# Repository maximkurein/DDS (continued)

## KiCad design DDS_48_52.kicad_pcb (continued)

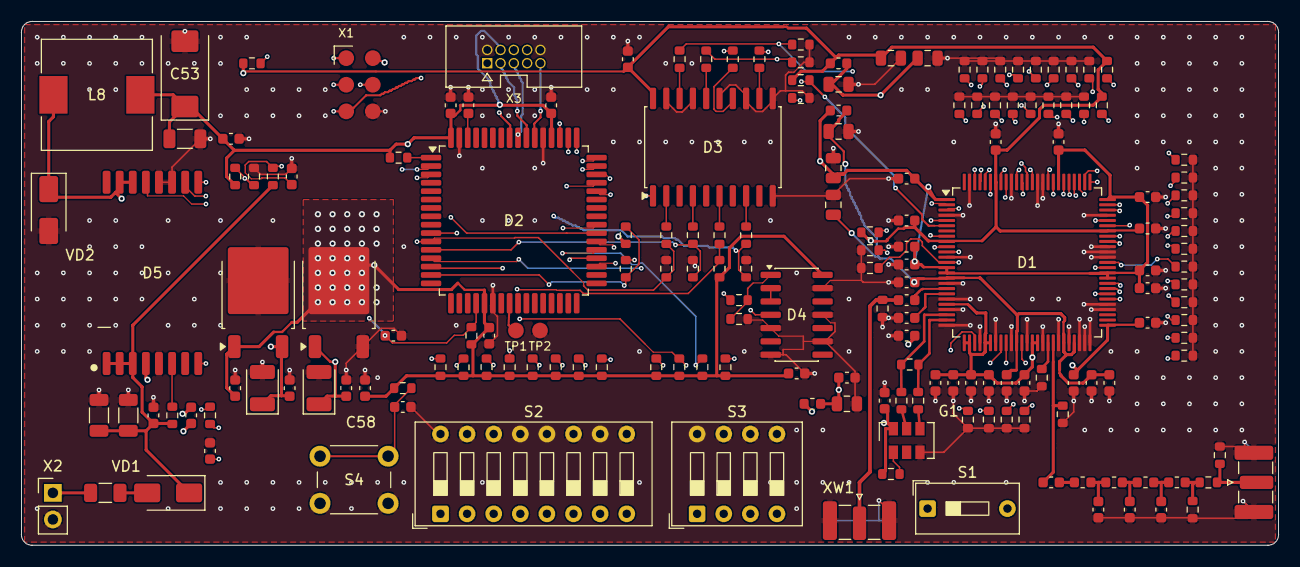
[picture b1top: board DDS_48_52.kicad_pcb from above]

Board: 4 copper layers, 120.0 x 50.0 mm, 178 parts (0 on the bottom side), 116 nets.

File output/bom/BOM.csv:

"Reference","Value","Footprint","Допуск","Мощность","Напряжение","ТКЕ","Примечание","QUANTITY","DNP"
"C1,C55,C56","1u","Capacitor_SMD:C_0603_1608Metric","","","16V","X7R","","3",""
"C2,C12-C18,C20-C23,C25-C27,C29-C36,C38-C45,C48,C50,C51,C54,C59,C60","100n","Capacitor_SMD:C_0603_1608Metric","","","50V","X7R","","37",""
"C3-C5","10n","Capacitor_SMD:C_0603_1608Metric","","","50V","C0G","","3",""
"C6,C11","56p","Capacitor_SMD:C_0603_1608Metric","2%","","50V","C0G","","2",""
"C7","91p","Capacitor_SMD:C_0603_1608Metric","2%","","50V","C0G","","1",""
"C8-C10,C19,C24,C28,C37","10u","Capacitor_SMD:C_0805_2012Metric","","","10V","X7R","","7",""
"C46,C47","10u","Capacitor_SMD:C_1206_3216Metric","","","25V","X7R","","2",""
"C49","220n","Capacitor_SMD:C_0603_1608Metric","","","50V","X7R","","1",""
"C52","22u","Capacitor_SMD:C_1206_3216Metric","","","10V","X7R","","1",""
"C53","100u","Capacitor_Tantalum_SMD:CP_EIA-7343-31_Kemet-D","","","10V","","танталовый (К53-65 — уточнить типоразмер); ESR задаёт ноль коррекции","1",""
"C57,C58","10u","Capacitor_Tantalum_SMD:CP_EIA-3528-21_Kemet-B","","","10V","","танталовый (К53-65 — уточнить типоразмер)","2",""
"D1","1508ПЛ8Т","DDS:LQFP-100_14x14mm_P0.5mm_1508PL8T","","","","","","1",""
"D2","1887ВЕ7Т","DDS:CQFP-64_4203.64-2_14x14mm_P0.8mm_1887VE7T","","","","","","1",""
"D3","1564АП3У2","DDS:SOIC-20W_1564AP3U2_PLACEHOLDER","","","","","буфер 5 -> 3,3 В, питание +3,3 В","1",""
"D4","1594ТЛ2Т","DDS:SOIC-14_1594TL2T_PLACEHOLDER","","","","","SDO 3,3 -> 5 В, питание +5 В","1",""
"D5","1393ЕУ014","DDS:4112.16-15.01_1393EU014_PLACEHOLDER","","","","","DC/DC +15 -> +5 В; корпус 4112.16-15.01 — посадочное место уточнить по чертежу","1",""
"D6","1158ЕН3.3ВХ","DDS:KT-93-1_PLACEHOLDER","","","","","LDO +3,3 В","1",""
"D7","1325ЕН1.8У","DDS:KT-93-1_PLACEHOLDER","","","","","LDO +1,8 В","1",""
"F1","0.5A","Fuse:Fuse_1206_3216Metric","","","","","","1",""
"G1","ГК361-ТК-02","DDS:OSC_6pad_5.0x3.2mm_P1.27mm_GK361_UNVERIFIED","","","","","480 МГц LVDS; распиновка и корпус НЕ ПОДТВЕРЖДЕНЫ паспортом","1","DNP"
"L1,L7","51n","Inductor_SMD:L_0603_1608Metric","2%","","","","ВЧ, Q >= 30 на 50 МГц","2",""
"L2-L4","600R@100MHz","Inductor_SMD:L_0603_1608Metric","","","","","ферритовый фильтр, Rdc <= 0,1 Ом, 1 А","3",""
"L5,L6","200n","Inductor_SMD:L_0603_1608Metric","2%","","","","ВЧ, Q >= 30 на 50 МГц","2",""
"L8","56u","DDS:L_10.4x10.4_L8_UNSELECTED_PLACEHOLDER","","","","","Силовой 56 мкГн; тип по перечню Минпромторга НЕ ВЫБРАН; ТУ и корпус уточнить","1",""
"R1","10k","Resistor_SMD:R_0603_1608Metric","5%","0,063 Вт","","","","1","DNP"
"R2","49.9R","Resistor_SMD:R_0603_1608Metric","1%","0,063 Вт","","","","1",""
"R3,R4","0R","Resistor_SMD:R_0603_1608Metric","","0,063 Вт","","","","2","DNP"
"R5,R7-R9,R48-R64,R67,R69,R72,R77-R80,R85","10k","Resistor_SMD:R_0603_1608Metric","5%","0,063 Вт","","","","29",""
"R6","100R","Resistor_SMD:R_0603_1608Metric","1%","0,063 Вт","","","","1",""
"R10,R13-R24,R28-R43,R82,R84","100k","Resistor_SMD:R_0603_1608Metric","5%","0,063 Вт","","","","31",""
"R11,R12","7.15k","Resistor_SMD:R_0603_1608Metric","0,1%","0,063 Вт","","","задаёт IFS = 72 В / R = 10,07 мА","2",""
"R25-R27,R44","49.9R","Resistor_SMD:R_0603_1608Metric","0,1%","0,063 Вт","","","","4",""
"R45","5.76R","Resistor_SMD:R_0603_1608Metric","1%","0,063 Вт","","","","1",""
"R46,R47","866R","Resistor_SMD:R_0603_1608Metric","1%","0,063 Вт","","","","2",""
"R65,R66,R68,R70,R71","1k","Resistor_SMD:R_0603_1608Metric","5%","0,063 Вт","","","ограничение тока защитных диодов 1564АП3","5",""
"R73-R76","33R","Resistor_SMD:R_0603_1608Metric","5%","0,063 Вт","","","","4",""
"R81","1k","Resistor_SMD:R_0603_1608Metric","5%","0,063 Вт","","","","1",""
"R83","909R","Resistor_SMD:R_0603_1608Metric","1%","0,063 Вт","","","порог тока ключа ≈ 1,6 А","1",""
"R86","40.2k","Resistor_SMD:R_0603_1608Metric","1%","0,063 Вт","","","","1",""
"R87","10k","Resistor_SMD:R_0603_1608Metric","1%","0,063 Вт","","","","1",""
"R88","47k","Resistor_SMD:R_0603_1608Metric","5%","0,063 Вт","","","признак +3,3 В для МК","1",""
"S1","DIP-1","Button_Switch_THT:SW_DIP_SPSTx01_Slide_9.78x4.72mm_W7.62mm_P2.54mm","","","","","CSEL: замкнут = внешний такт (XW1)","1",""
"S2","DIP-8","Button_Switch_THT:SW_DIP_SPSTx08_Slide_9.78x22.5mm_W7.62mm_P2.54mm","","","","","биты 0–7 кода частоты","1",""
"S3","DIP-4","Button_Switch_THT:SW_DIP_SPSTx04_Slide_9.78x12.34mm_W7.62mm_P2.54mm","","","","","биты 8–11 кода частоты","1",""
"S4","6x6","Button_Switch_THT:SW_PUSH_6mm","","","","","«Применить»","1",""
"VD1","SS34","Diode_SMD:D_SMA","","","","","","1",""
"VD2","2Д2990А","DDS:D_SMA_2D2990A_PLACEHOLDER","","","","","диод DC/DC: >= 2 А, >= 40 В (параметры и корпус — уточнить по ТУ)","1",""
"X2","PLS-2","Connector_PinHeader_2.54mm:PinHeader_1x02_P2.54mm_Vertical","","","","","вход +15 В","1",""
"X3","SHF-105-01-L-D-TH","DDS:Samtec_SHF-105-01-L-D-TH","","","","","AVR JTAG Atmel-ICE, 2x5, шаг 1,27 мм; VTG только контроль +5 В","1",""
"XW1","SMA","Connector_Coaxial:SMA_Samtec_SMA-J-P-H-ST-EM1_EdgeMount","","","","","вход 480 МГц, 0 дБм, 50 Ом","1",""
"XW2","SMA","Connector_Coaxial:SMA_Samtec_SMA-J-P-H-ST-EM1_EdgeMount","","","","","выход 48–52 МГц, −10 дБм, 50 Ом","1",""

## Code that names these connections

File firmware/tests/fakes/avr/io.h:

/* Host-only register stand-ins; selected by the regression test include path. */
#ifndef TEST_AVR_IO_H
#define TEST_AVR_IO_H
#include <stdint.h>
#define _BV(bit) (1u << (bit))
enum { PB0, PB1, PB2, PB3, PB4, PB5, PB6, PB7 };
enum { PC0, PC1, PC2, PC3, PC4, PC5, PC6, PC7 };
extern uint8_t PORTA, DDRA, PINA, PORTB, DDRB, PINB, PORTC, DDRC, PINC;
extern uint8_t PORTD, DDRD, PORTE, DDRE, PORTF, DDRF, PORTG, DDRG, OSCCAL;
#endif

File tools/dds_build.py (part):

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    sh.flag(g2[0] + 5.08, g2[1], (0, -1))
    sh.text('+15 В ±5 %', 22.86, Y - 8.89, 1.524)
    sh.flag(73.66, Y, (0, 1))
    sh.label('VIN_PROT', 72.39, Y, (1, 0))

    # ---- DC/DC 1393ЕУ014: +15 В -> +5 В ------------------------------------
    x0 = 127.0
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    sh.wire((nx, yb), c44.pin_xy(1)); sh.wired_pins.add(('C44', '1'))
    term(sh, c44, 2, 0)
    sh.wire((nx, yb), (nx, yb - 2.54))
    sh.label('APPLYn', nx, yb - 2.54, (1, 0))

    yr = yb + 30.48
    r37 = put(sh, 'R37', xa + 7.62, yr, ang=90)
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    c39 = put(sh, 'C39', nx, yr + 5.08)
    sh.wire((nx, yr), c39.pin_xy(1)); sh.wired_pins.add(('C39', '1'))
    term(sh, c39, 2, 0)
    sh.label('MCU_RESETn', nx + 10.16, yr, (1, 0), kind='global')

    isp = put(sh, 'J5', 314.96, 223.52)
    put(sh, 'J101', 215.9, 281.94)
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        else:
            sh.wire(ro.pin_xy(1), (ro.x, yy)); sh.wired_pins.add((rout, '1'))
            term(sh, ro, 2, 0)
    # EN (1OE#): BUF_OEn with pull-up to +3V3 (MCU pin in Hi-Z -> outputs off),
    # 1 кОм series resistor R110 to the 3,3 V input
    ex, ey = b.pin_xy('1')
    r110 = put(sh, 'R110', ex - 10.16, ey, ang=90)
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    ax, ay = g1.pin_xy('1')
    r55 = put(sh, 'R55', ax - 22.86, ay, ang=90)
    sh.pin_wire(r55, 1, (r55.pin_xy(1)[0] - 10.16, ay))
    wl(sh, 'DDS_SDO', r55.pin_xy(1)[0] - 10.16, ay, (-1, 0))
    sh.connect(r55, 2, g1, '1')
    sh.label(NET[('U7', '1')], ax - 5.08, ay, (-1, 0))
    r56 = put(sh, 'R56', ax - 12.7, ay + 7.62)
    sh.wire(r56.pin_xy(1), (r56.x, ay)); sh.wired_pins.add(('R56', '1'))
    term(sh, r56, 2, 0)
    sh.connect(g1, '2', g2_, '3')
    sh.label('SDO_INV', g1.pin_xy('2')[0] + 2.54, ay, (1, 0))
    for u, x in ((3, 360.68), (4, 391.16), (5, 421.64), (6, 452.12)):
        put(sh, 'U7', x, 330.2, unit=u)
    gp = put(sh, 'U7', 488.95, 330.2, unit=7)
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    xr = d1.pin_xy(43)[0]          # right pin connection x

    # ---- clock inputs ---------------------------------------------------
    clkp, clkm = d1.pin_xy(24), d1.pin_xy(23)
    r69 = put(sh, 'R69', xp - 10.16, clkp[1])
    r69.ref_pos = (r69.x - 2.54, r69.y - 0.635, 'right bottom'); r69.val_pos = (r69.x - 2.54, r69.y + 0.635, 'right top')
    sh.pin_wire(d1, 24, (xp - 5.08, clkp[1]), (xp - 5.08, r69.pin_xy(1)[1]), r69.pin_xy(1))
    sh.wired_pins.add(('R69', '1'))
    sh.pin_wire(d1, 23, r69.pin_xy(2))
    sh.wired_pins.add(('R69', '2'))
    sh.wire(r69.pin_xy(1), (xp - 20.32, r69.pin_xy(1)[1]))
    sh.label('CLKP', xp - 20.32, r69.pin_xy(1)[1], (-1, 0))
    sh.wire(r69.pin_xy(2), (xp - 20.32, clkm[1]))
    sh.label('CLKM', xp - 20.32, clkm[1], (-1, 0))

    cdp = d1.pin_xy(18)
    xw1 = put(sh, 'J2', 81.28, cdp[1], mirror='y')
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    sh.wire((nx, cs[1]), r71.pin_xy(1)); sh.wired_pins.add(('R71', '1'))
    term(sh, r71, 2, 0)
    s1 = put(sh, 'DIP1', nx - 15.24, cs[1])
    sh.wire(s1.pin_xy(2), (nx, cs[1])); sh.wired_pins.add(('DIP1', '2'))
    term(sh, s1, 1, 0)
    sh.text('{DIP1} замкнут: такт с {J2} (CLKD); разомкнут: {G1} (CLKP/M)', 66.04, cs[1] + 15.24, 1.27)

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
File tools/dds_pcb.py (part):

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            '27': 'C20', '30': 'C21', '31': 'C22', '36': 'C23', '39': 'C24', '40': 'C25', '45': 'C26',
            '47': 'C27', '51': 'C28', '60': 'C29', '61': 'C30', '69': 'C31', '75': 'C32', '82': 'C33',
            '94': 'C34'}
    ko = {'B': (0.6, 3.6)}           # RF channel under pins 41..44 (OUTM1/OUTP1)
    clk_caps = [(R('C49'), '18', inner_pin(proj, R('C49'), pn('18'))),
                (R('C50'), '19', inner_pin(proj, R('C50'), pn('19')))]
    ring(proj, fps, U1, [(R(c), p, inner_pin(proj, R(c), pn(p))) for p, c in cmap.items()] + clk_caps,
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        gnd_pin1 = proj.pin_net[(R(ref), '1')] == 'GND'
        put(fps, R(ref), x, yy, (90 if gnd_pin1 else 270) if down else (270 if gnd_pin1 else 90))
    put(fps, R('J3'), BW - 2.1, y, 0)            # SMA output, edge launch to +x
    # 480 MHz clock inputs.  D1 left side, top to bottom: CLKDP/CLKDM (pins 18/19,
    # external clock via XW1) then CLKM/CLKP (pins 23/24, LVDS from G1).  To keep
    # both paths on F.Cu over the solid In1 GND plane without crossing, the
    # external line runs north at x = 81 and the oscillator group sits below the
    # D1 corner, its pair entering pins 23/24 from below (see clock_routes()).
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
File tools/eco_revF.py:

"""Revision F additions; stable keys do not renumber the revision E drawing."""
NEW_REFS = {'J101': 'X3', 'TP101': 'TP1', 'TP102': 'TP2'}
MCU_PINS = {'54': 'JTAG_TDI', '55': 'JTAG_TDO', '56': 'JTAG_TMS',
            '57': 'JTAG_TCK', '24': 'MCU_BQ1_RECOVERY'}
NETS = {
    'J101': {'1': 'JTAG_TCK', '2': 'GND', '3': 'JTAG_TDO', '4': '+5V',
             '5': 'JTAG_TMS', '6': 'MCU_RESETn', '7': 'unconnected-X3-7',
             '8': 'unconnected-X3-8', '9': 'JTAG_TDI', '10': 'GND'},
    'TP101': {'1': 'MCU_BQ1_RECOVERY'},
    'TP102': {'1': 'GND'},
}


def apply(net):
    for p, n in MCU_PINS.items():
        net[('U2', p)] = n
    for k, pins in NETS.items():
        for p, n in pins.items():
            net[(k, p)] = n

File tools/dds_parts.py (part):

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    if ref.startswith('SW'):
        k = int(ref[2:])
        if 1 <= k <= 8:
            return 'DIP8', k, (None if pin is None else (str(k) if pin == '1' else str(17 - k)))
        if 9 <= k <= 12:
            j = k - 8
            return 'DIP4', j, (None if pin is None else (str(j) if pin == '1' else str(9 - j)))
        if k == 14:
            return 'DIP1', 1, pin
        if k == 13:
            return 'BTN', 1, pin
    return ref, None, pin
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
